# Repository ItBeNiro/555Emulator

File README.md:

# 555Emulator
An open source emulator for the 555 timer. On a single PCB, it allows probing of comparators, flip-flops, and more! A great way to learn about the basics of microchips using discrete components.

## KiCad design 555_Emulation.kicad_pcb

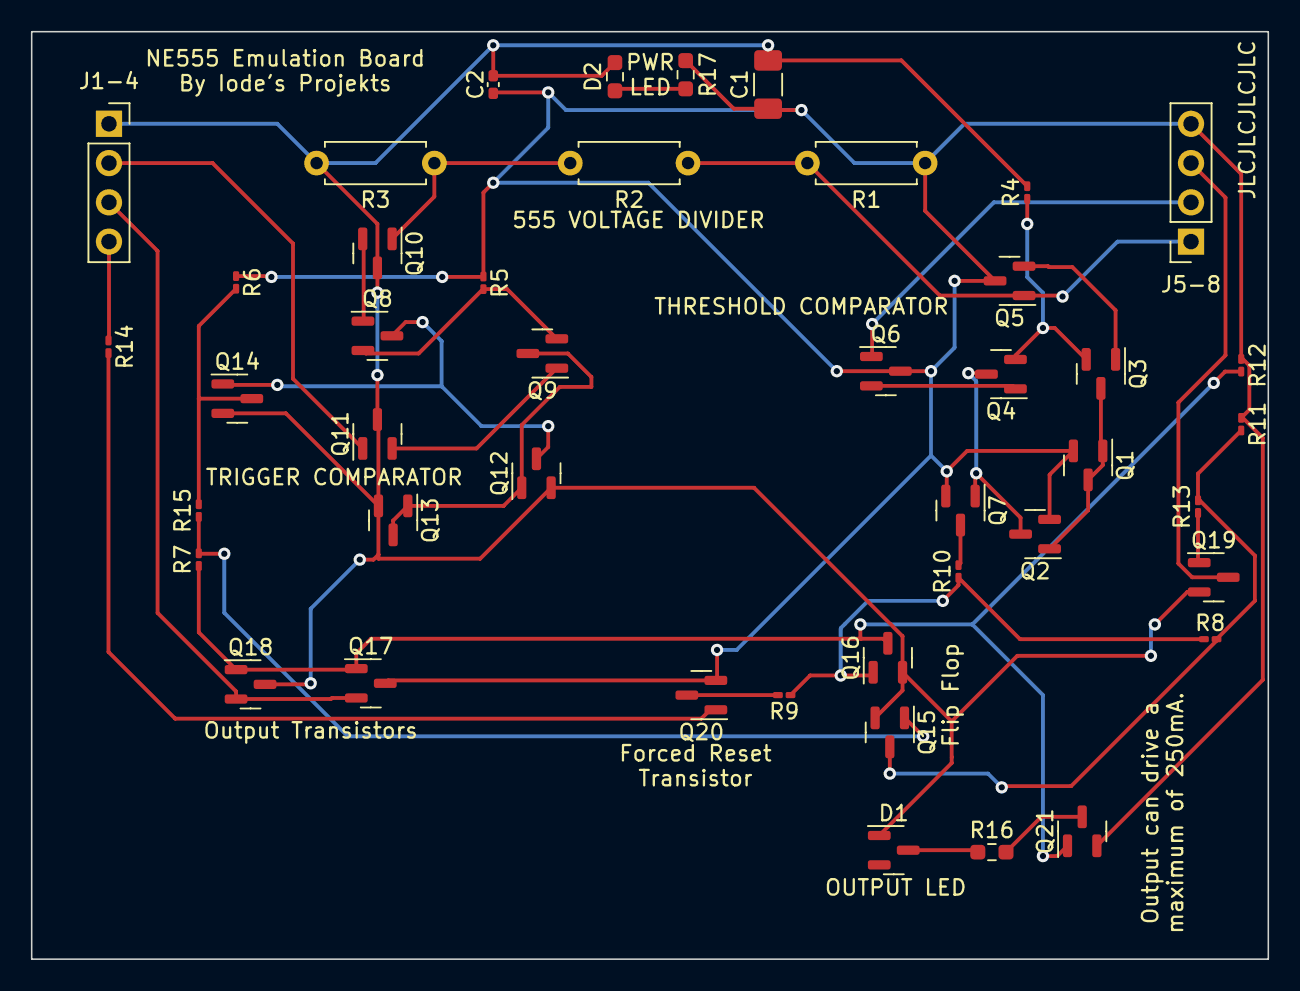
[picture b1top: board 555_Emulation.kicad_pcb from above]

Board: 2 copper layers, 80.0 x 60.0 mm, 44 parts (0 on the bottom side), 31 nets.

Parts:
C1: 100uf; C_1206_3216Metric_Pad1.33x1.80mm_HandSolder
C2: 10nf; C_0402_1005Metric_Pad0.74x0.62mm_HandSolder
D1: Green LED; SOT-23
D2: Red LED; R_0603_1608Metric_Pad0.98x0.95mm_HandSolder
J1-4, J5-8: Screw_Terminal_01x04; PinSocket_1x04_P2.54mm_Vertical
Q1, Q2, Q7: Q_PNP_BCE; SOT-23-BCE
Q3, Q4, Q5, Q6, Q12, Q13, Q14, Q15, Q16, Q17, Q19: Q_NPN_BCE; SOT-23-BCE
Q8, Q9, Q10, Q11, Q18, Q20, Q21: Q_PNP_CEB; SOT-23-CEB
R1, R2, R3: 5k; R_Axial_DIN0207_L6.3mm_D2.5mm_P7.62mm_Horizontal
R4, R5: 10k; R_0201_0603Metric_Pad0.64x0.40mm_HandSolder
R6, R7, R8, R9, R10, R13, R15: 5k; R_0201_0603Metric_Pad0.64x0.40mm_HandSolder
R11, R12, R14: 1k; R_0201_0603Metric_Pad0.64x0.40mm_HandSolder
R16, R17: 160; R_0603_1608Metric_Pad0.98x0.95mm_HandSolder

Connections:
CONT: J5-8.1, Q5.1 (B), R1.2, R2.1
DSCH: J5-8.3, Q19.2 (C)
GND: C1.2, C2.2, D1.1, D2.2 (A), J1-4.1, Q10.1 (C), Q11.1 (C), Q12.3 (E), Q13.3 (E), Q14.3 (E), Q15.3 (E), Q16.3 (E), Q18.1 (C), Q19.3 (E), R3.2, R4.2
unnamed: D1.3, R16.1
unnamed: D2.1 (K), R17.2
unnamed: Q1.1 (B), Q1.2 (C), Q2.1 (B), Q3.2 (C)
unnamed: Q2.2 (C), Q4.2 (C), Q7.1 (B)
unnamed: Q3.1 (B), Q5.3 (E)
unnamed: Q3.3 (E), Q4.3 (E), R4.1
unnamed: Q4.1 (B), Q6.3 (E)
unnamed: Q8.2 (E), Q9.2 (E), R5.2
unnamed: Q8.3 (B), Q10.2 (E)
unnamed: Q10.3 (B), R2.2, R3.1
unnamed: Q9.3 (B), Q11.2 (E)
unnamed: Q9.1 (C), Q12.1 (B), Q13.1 (B), Q13.2 (C)
unnamed: Q8.1 (C), Q12.2 (C), Q14.1 (B)
unnamed: Q14.2 (C), R6.2, R15.2
unnamed: Q15.1 (B), R7.2, R15.1
unnamed: Q15.2 (C), R8.2, R11.2, R13.2
unnamed: Q16.1 (B), R8.1, R9.1, R10.1
unnamed: Q16.2 (C), Q17.1 (B), Q18.3 (B), Q21.3 (B), R7.1, R12.2
unnamed: Q19.1 (B), R13.1
unnamed: Q20.1 (C), R9.2
unnamed: Q20.3 (B), R14.2
unnamed: Q21.1 (C), R16.2
OUT: J1-4.3, Q17.3 (E), Q18.2 (E)
RESET: J1-4.4, R14.1
RST: Q7.2 (C), R10.2
THRES: J5-8.2, Q6.1 (B)
TRIG: J1-4.2, Q11.3 (B)
VCC: C1.1, C2.1, J5-8.4, Q1.3 (E), Q2.3 (E), Q5.2 (C), Q6.2 (C), Q7.3 (E), Q17.2 (C), Q20.2 (E), Q21.2 (E), R1.1, R5.1, R6.1, R11.1, R12.1, R17.1

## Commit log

2022-03-28 Add files via upload
    Uploading all files at the end of project.
